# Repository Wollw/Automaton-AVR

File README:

Automaton AVR
====
This program simulates a Celullar Automaton with an AVR MCU connected to:
	(2) 4021 parallel->serial shift registers for reading
		survival rules from dip switches
	(2) 4021 parallel->serial shift registers for reading
		birth rules from dip switches
	(3) 4021 used to read initial cell state from
	(3) 74HC595 for controlling 24 different LEDs

Installation
----
Pick a configuration:
    $ cp cfg/myconfig.h src/config.h

To build:
    $ make

To upload:
    $ make program

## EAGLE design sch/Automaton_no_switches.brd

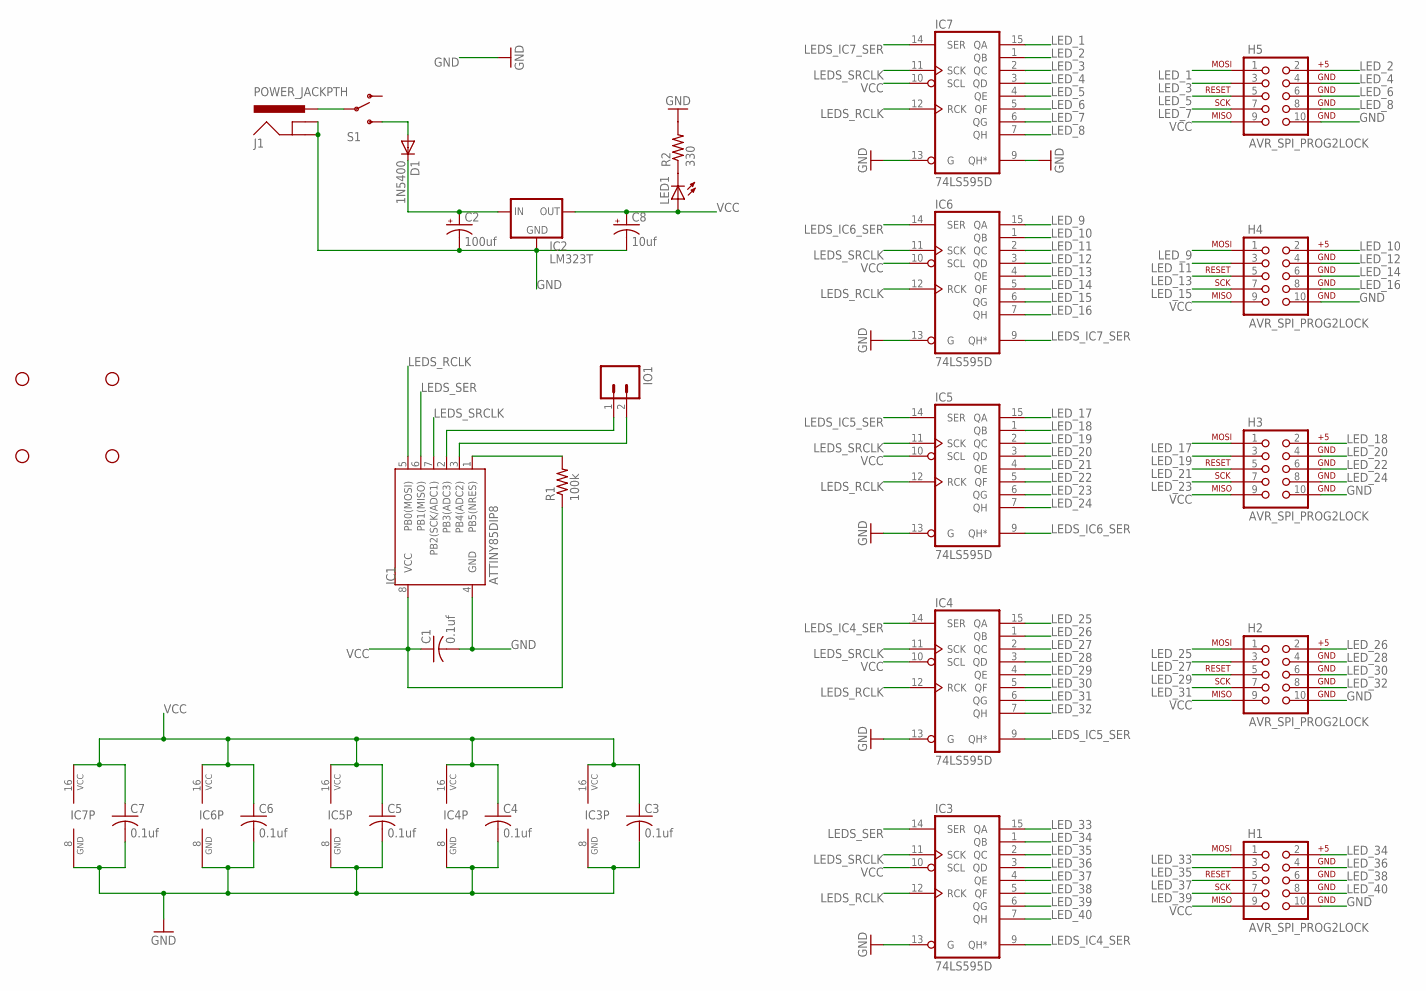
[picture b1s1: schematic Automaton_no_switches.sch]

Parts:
C1, C3, C4, C5, C6, C7: 0.1uf; C1206
C2: 100uf; E5-10,5
C8: 10uf; E2-5
D1: 1N5400; DO201-15
H1, H2, H3, H4, H5: AVR_SPI_PROG2LOCK; 2X5-SHROUDED_LOCK
HOLE1, HOLE2, HOLE3, HOLE4: STAND-OFF
IC1: ATTINY85DIP8; DIP08
IC2: LM323T; TO220-IGO
IC3, IC4, IC5, IC6, IC7: 74LS595D; SO16
IO1: M02PTH3; 1X02_LONGPADS
J1: POWER_JACKPTH; POWER_JACK_PTH
LED1: LEDSMT1206; 1206
R1: 100k; M1206
R2: 330; M1206
S1: SWITCH-SPDTPTH_LOCK; SWITCH-SPDT_LOCK.007S

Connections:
GND: C1.2, C2.-, C3.2, C4.2, C5.2, C6.2, C7.2, C8.-, H1.10, H2.10, H3.10, H4.10, H5.10, IC1.4 (GND), IC2.GND, IC3.8 (GND), IC3.13 (G), IC4.8 (GND), IC4.13 (G), IC5.8 (GND), IC5.13 (G), IC6.8 (GND), IC6.13 (G), IC7.8 (GND), IC7.9 (QH*), IC7.13 (G), J1.GND, J1.GNDBREAK, R2.2
LEDS_IC4_SER: IC3.9 (QH*), IC4.14 (SER)
LEDS_IC5_SER: IC4.9 (QH*), IC5.14 (SER)
LEDS_IC6_SER: IC5.9 (QH*), IC6.14 (SER)
LEDS_IC7_SER: IC6.9 (QH*), IC7.14 (SER)
LEDS_RCLK: IC1.5 (PB0(MOSI)), IC3.12 (RCK), IC4.12 (RCK), IC5.12 (RCK), IC6.12 (RCK), IC7.12 (RCK)
LEDS_SER: IC1.6 (PB1(MISO)), IC3.14 (SER)
LEDS_SRCLK: IC1.7 (PB2(SCK/ADC1)), IC3.11 (SCK), IC4.11 (SCK), IC5.11 (SCK), IC6.11 (SCK), IC7.11 (SCK)
LED_1: H5.1, IC7.15 (QA)
LED_2: H5.2, IC7.1 (QB)
LED_3: H5.3, IC7.2 (QC)
LED_4: H5.4, IC7.3 (QD)
LED_5: H5.5, IC7.4 (QE)
LED_6: H5.6, IC7.5 (QF)
LED_7: H5.7, IC7.6 (QG)
LED_8: H5.8, IC7.7 (QH)
LED_9: H4.1, IC6.15 (QA)
LED_10: H4.2, IC6.1 (QB)
LED_11: H4.3, IC6.2 (QC)
LED_12: H4.4, IC6.3 (QD)
LED_13: H4.5, IC6.4 (QE)
LED_14: H4.6, IC6.5 (QF)
LED_15: H4.7, IC6.6 (QG)
LED_16: H4.8, IC6.7 (QH)
LED_17: H3.1, IC5.15 (QA)
LED_18: H3.2, IC5.1 (QB)
LED_19: H3.3, IC5.2 (QC)
LED_20: H3.4, IC5.3 (QD)
LED_21: H3.5, IC5.4 (QE)
LED_22: H3.6, IC5.5 (QF)
LED_23: H3.7, IC5.6 (QG)
LED_24: H3.8, IC5.7 (QH)
LED_25: H2.1, IC4.15 (QA)
LED_26: H2.2, IC4.1 (QB)
LED_27: H2.3, IC4.2 (QC)
LED_28: H2.4, IC4.3 (QD)
LED_29: H2.5, IC4.4 (QE)
LED_30: H2.6, IC4.5 (QF)
LED_31: H2.7, IC4.6 (QG)
LED_32: H2.8, IC4.7 (QH)
LED_33: H1.1, IC3.15 (QA)
LED_34: H1.2, IC3.1 (QB)
LED_35: H1.3, IC3.2 (QC)
LED_36: H1.4, IC3.3 (QD)
LED_37: H1.5, IC3.4 (QE)
LED_38: H1.6, IC3.5 (QF)
LED_39: H1.7, IC3.6 (QG)
LED_40: H1.8, IC3.7 (QH)
unnamed: C2.+, D1.C, IC2.IN
unnamed: IC1.1 (PB5(NRES)), R1.2
unnamed: J1.PWR, S1.2
unnamed: D1.A, S1.3 (S)
unnamed: LED1.C, R2.1
PB3: IC1.2 (PB3(ADC3)), IO1.1
PB4: IC1.3 (PB4(ADC2)), IO1.2
VCC: C1.1, C3.1, C4.1, C5.1, C6.1, C7.1, C8.+, H1.9, H2.9, H3.9, H4.9, H5.9, IC1.8 (VCC), IC2.OUT, IC3.10 (SCL), IC3.16 (VCC), IC4.10 (SCL), IC4.16 (VCC), IC5.10 (SCL), IC5.16 (VCC), IC6.10 (SCL), IC6.16 (VCC), IC7.10 (SCL), IC7.16 (VCC), LED1.A, R1.1

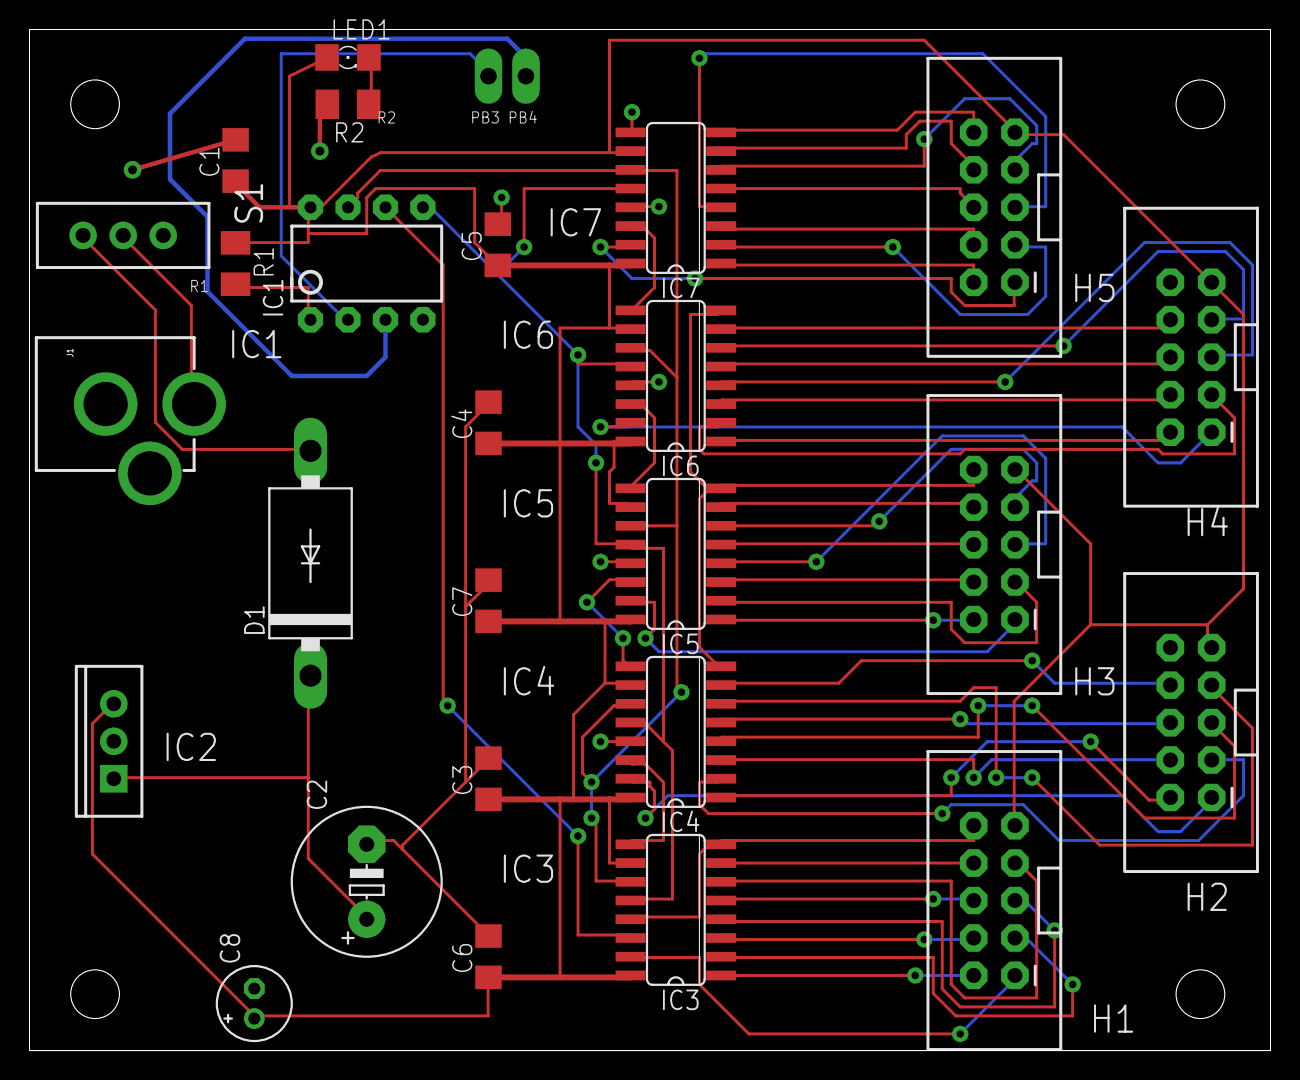
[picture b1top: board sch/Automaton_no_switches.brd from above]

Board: 2 copper layers, 84.1 x 69.2 mm, 31 parts (0 on the bottom side), 56 nets.

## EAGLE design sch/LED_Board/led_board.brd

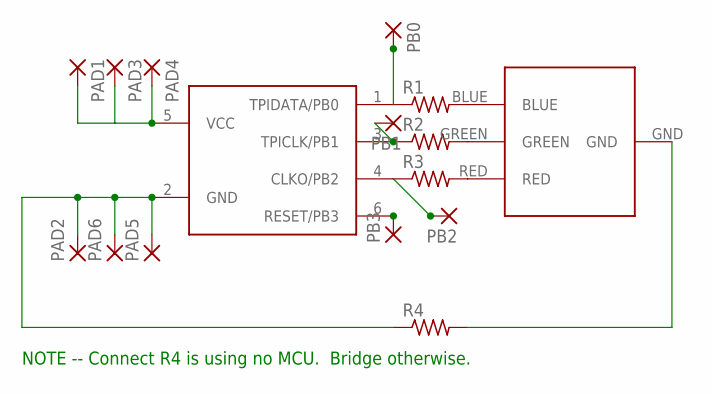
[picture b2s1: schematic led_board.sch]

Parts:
PAD1, PAD2, PAD3, PAD4, PAD5, PAD6: 1,6/0,8
PB0, PB1, PB2, PB3: 1,6/0,8
R1, R2, R3, R4: R-US_M1206; M1206
U$1: BIVAR-RGB-LED; 7.6X7.6MM-LED
U$2: ATTINY10SOT; SOT23-6

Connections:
unnamed: PAD2.1, PAD5.1, PAD6.1, R4.1, U$2.2 (GND)
unnamed: R1.2, U$1.BLUE
unnamed: R2.2, U$1.GREEN
unnamed: R3.2, U$1.RED
unnamed: R4.2, U$1.GND
PB0: PB0.1, R1.1, U$2.1 (TPIDATA/PB0)
PB1: PB1.1, R2.1, U$2.3 (TPICLK/PB1)
PB2: PB2.1, R3.1, U$2.4 (CLKO/PB2)
PB3: PB3.1, U$2.6 (RESET/PB3)
VCC: PAD1.1, PAD3.1, PAD4.1, U$2.5 (VCC)

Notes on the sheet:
NOTE -- Connect R4 is using no MCU. Bridge otherwise.

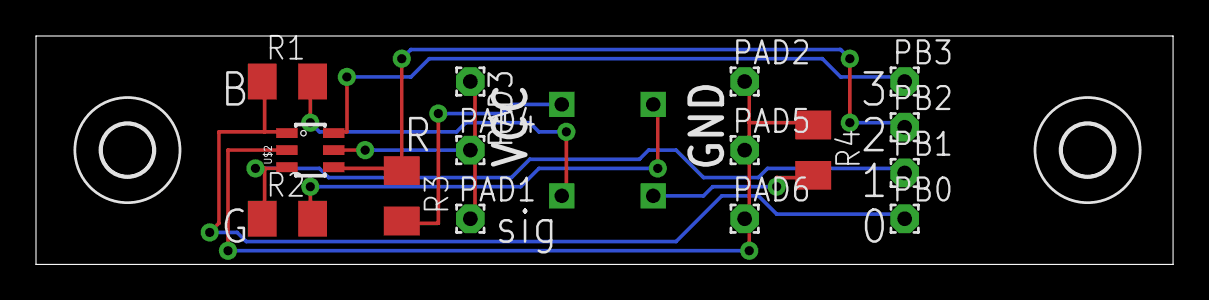
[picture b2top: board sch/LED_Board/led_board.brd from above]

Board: 2 copper layers, 63.2 x 12.7 mm, 18 parts (1 on the bottom side), 10 nets.

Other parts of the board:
E$1, E$2: 2,8

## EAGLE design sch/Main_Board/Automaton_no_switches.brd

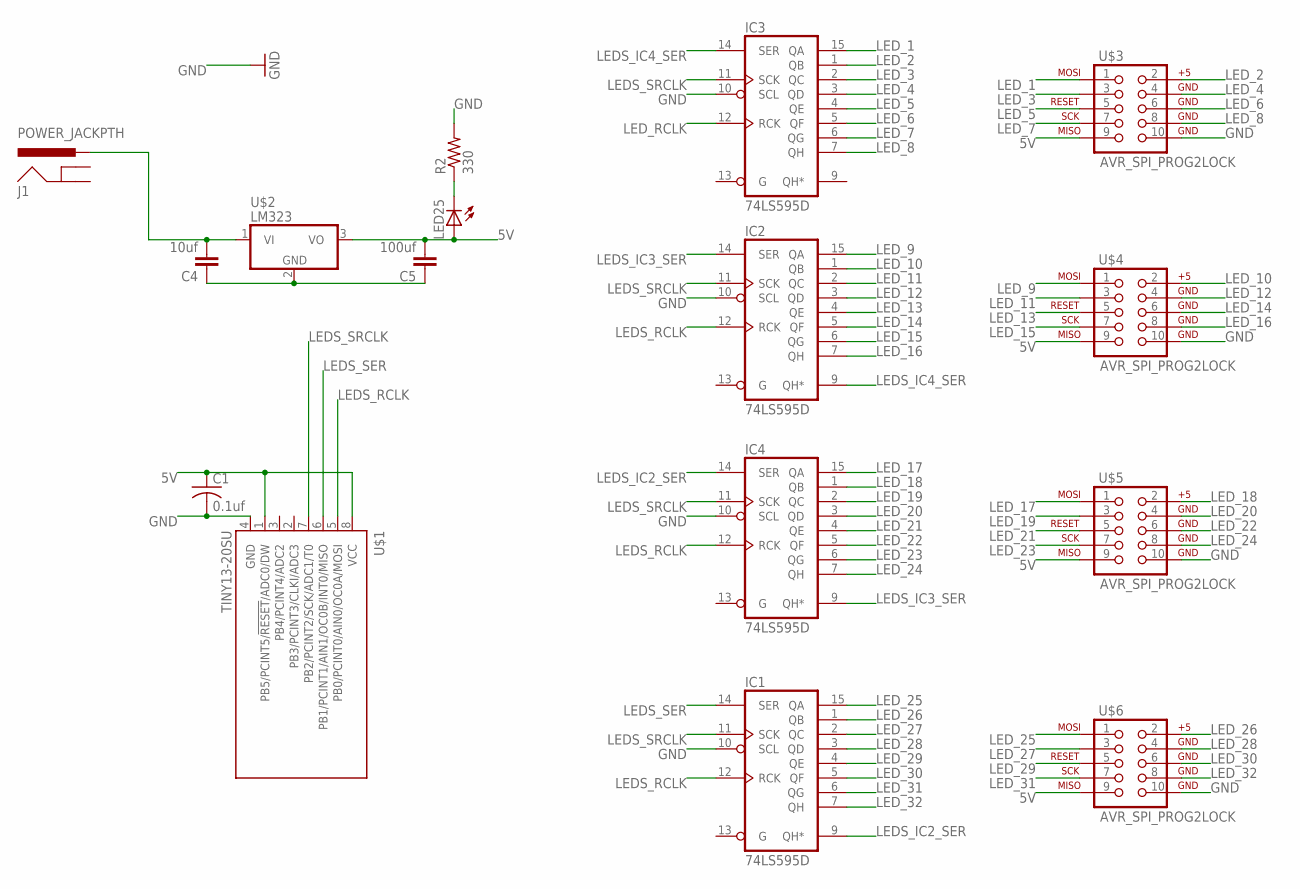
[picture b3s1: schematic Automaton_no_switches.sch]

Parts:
C1: 0.1uf; C025-024X044
C4: 10uf; 1210
C5: 100uf; 1210
IC1, IC2, IC3, IC4: 74LS595D; SO16
J1: POWER_JACKPTH; POWER_JACK_PTH
LED25: LED; SMARTLED-TTW
R2: 330; 0204/5
U$1: TINY13-20SU; 8S2
U$2: LM323; TO220H
U$3, U$4, U$5, U$6: AVR_SPI_PROG2LOCK; 2X5-SHROUDED_LOCK

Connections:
5V: C1.1, C5.2, LED25.A@1 (A), U$1.1 (PB5/PCINT5/!RESET!/ADC0/DW), U$1.8 (VCC), U$2.3 (VO), U$3.9, U$4.9, U$5.9, U$6.9
GND: C1.2, IC1.8 (GND), IC1.10 (SCL), IC2.8 (GND), IC2.10 (SCL), IC3.8 (GND), IC3.10 (SCL), IC4.8 (GND), IC4.10 (SCL), R2.2, U$1.4 (GND), U$3.10, U$4.10, U$5.10, U$6.10
LEDS_IC2_SER: IC1.9 (QH*), IC4.14 (SER)
LEDS_IC3_SER: IC2.14 (SER), IC4.9 (QH*)
LEDS_IC4_SER: IC2.9 (QH*), IC3.14 (SER)
LEDS_RCLK: IC1.12 (RCK), IC2.12 (RCK), IC4.12 (RCK), U$1.5 (PB0/PCINT0/AIN0/OC0A/MOSI)
LEDS_SER: IC1.14 (SER), U$1.6 (PB1/PCINT1/AIN1/OC0B/INT0/MISO)
LEDS_SRCLK: IC1.11 (SCK), IC2.11 (SCK), IC3.11 (SCK), IC4.11 (SCK), U$1.7 (PB2/PCINT2/SCK/ADC1/T0)
LED_1: IC3.15 (QA), U$3.1
LED_2: IC3.1 (QB), U$3.2
LED_3: IC3.2 (QC), U$3.3
LED_4: IC3.3 (QD), U$3.4
LED_5: IC3.4 (QE), U$3.5
LED_6: IC3.5 (QF), U$3.6
LED_7: IC3.6 (QG), U$3.7
LED_8: IC3.7 (QH), U$3.8
LED_9: IC2.15 (QA), U$4.1
LED_10: IC2.1 (QB), U$4.2
LED_11: IC2.2 (QC), U$4.3
LED_12: IC2.3 (QD), U$4.4
LED_13: IC2.4 (QE), U$4.5
LED_14: IC2.5 (QF), U$4.6
LED_15: IC2.6 (QG), U$4.7
LED_16: IC2.7 (QH), U$4.8
LED_17: IC4.15 (QA), U$5.1
LED_18: IC4.1 (QB), U$5.2
LED_19: IC4.2 (QC), U$5.3
LED_20: IC4.3 (QD), U$5.4
LED_21: IC4.4 (QE), U$5.5
LED_22: IC4.5 (QF), U$5.6
LED_23: IC4.6 (QG), U$5.7
LED_24: IC4.7 (QH), U$5.8
LED_25: IC1.15 (QA), U$6.1
LED_26: IC1.1 (QB), U$6.2
LED_27: IC1.2 (QC), U$6.3
LED_28: IC1.3 (QD), U$6.4
LED_29: IC1.4 (QE), U$6.5
LED_30: IC1.5 (QF), U$6.6
LED_31: IC1.6 (QG), U$6.7
LED_32: IC1.7 (QH), U$6.8
LED_RCLK: IC3.12 (RCK)
unnamed: C4.2, J1.PWR, U$2.1 (VI)
unnamed: C4.1, C5.1, U$2.2 (GND)
unnamed: LED25.C@1 (C), R2.1
VCC: IC1.16 (VCC), IC2.16 (VCC), IC3.16 (VCC), IC4.16 (VCC)

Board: 2 copper layers, 16 parts (0 on the bottom side), 44 nets, no tracks yet.

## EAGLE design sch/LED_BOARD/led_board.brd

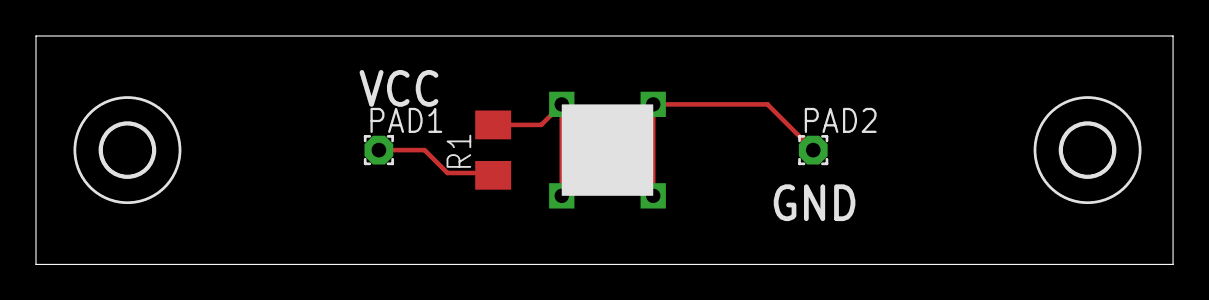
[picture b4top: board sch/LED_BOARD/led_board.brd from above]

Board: 2 copper layers, 63.2 x 12.7 mm, 6 parts (0 on the bottom side), 3 nets.

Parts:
E$1, E$2: 2,8
PAD1, PAD2: 1,6/0,8
R1: M1206
U$1: 7.6X7.6_LED; 7.6X7.6MM_LED

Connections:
GND: PAD2.1, U$1.GND1, U$1.GND2
unnamed: R1.2, U$1.VCC1, U$1.VCC2
VCC: PAD1.1, R1.1

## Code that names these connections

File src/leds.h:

#pragma once
#include <stdlib.h>
#include <stdint.h>
#include "petridish.h"

// shift registers (74HC595) for LEDs
#define LEDS_SHIFT_REG_COUNT	3

// Serial->Parallel for LEDs - Might change to PORTC to leave SPI open
#define LEDS_DDR	DDRB
#define LEDS_PORT   PORTB
#define LEDS_RCLK   PB0
#define LEDS_SER	PB1
#define LEDS_SRCLK  PB2

// Functions for interacting with the output for leds
// See leds.c for details
void leds_shift_init(void);
void leds_change_state(uint64_t new_state, uint8_t pins_to_shift);

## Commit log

2011-08-23 comment changes
2011-08-23 accidently committed the wrong thing before
2011-08-24 Cleaned the code up a bit and uses less memory.
2011-08-24 fixed gitignore file
2011-08-24 Changed ms_delay to scale based on defined MHZ. It only worked properly at 1MHz before.
2011-08-24 added using clock interrupt to TODO list
2011-08-24 multiple versions now
2011-08-28 Forgot a call to free
2011-08-28 fixing last commit, added to TODO list
2011-08-28 removing penrose as submodule. It was never meant to be one to begin with...
2011-08-29 oops... I called it penrose but it's actually the polygon automaton...
2011-08-30 Lots of fixes... still not quite working but thought I'd commit anyway. Using bitmaps instead of full variables for setting neighbors to save memory, divided much of the program into different functi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
2011-08-31 Everything works. Yay\!
2011-08-31 Changes rules to use an if statement with a rotated and AND'ed bitmask instead of a switch statement.
2011-08-31 moved initial state to a bitmask too
2011-08-31 mcu now assumed to be running at 1MHz
2011-08-31 added #define for staggering speed
2011-09-01 made STAGGER_DELAY_MS #define for defining the step of the stagger delay
2011-09-01 fixed a few small things and changed the way avr-size reports size data during make
2011-09-18 shift registers working in seperate program. still needs to be merged into main program (and I need to actually write the correct code for the piece I'm actually building too...)
2011-09-19 modularized the shift-registers program, created new directory for working on squares-and-triangles tessellation
2011-09-21 cleaned architecture a bit. added code for reading initial_state. new init code for the automaton. petridish_t data type acts as object for the automaton's state
2011-09-21 nothing major. commented out some redundant code
2011-09-23 WIP currently has a working Conway's blinker if rules dip switches are set to 2/23 rule set (Conway's Game of Life). Code for Initial State is present but untested and not currently in use as I haven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
2011-09-23 cleaned up debug code a bit. serial outputs the new petridish state after it calculates it
2011-09-23 cleaned source up a bit.
2011-09-23 deleted old parts of the project. cleaned up the build process a tad.
2011-09-23 added schematic that I'm working on. still largely incomplete
2011-10-03 cleaned main function a bit
2011-10-04 worked on schematic some more
2011-10-05 Done with schematic.
2011-10-05 Cleaned up schematic folder.
2011-10-16 Version 1! All the basics are in! DIP switches control rules and initial state. schematic is out of date.
2011-10-17 fixed some text in the readme
2011-10-17 Added BSD license.
2011-10-17 changed all expanded tabs to real tabs
2011-10-18 Using function pointers for petridish now. Makes for a larger program but I think it's cleaner. Also added a lot more comments.
2011-10-18 changed suffix of readme
2011-10-18 added README back
2011-10-18 renamed petridish struct to automaton. worked on comments more. working on making the automaton type more object like
2011-10-19 added configuration example and some text in readme. changed the way the automaton is created to malloc for a struct pointer; I think this is cleaner.
2011-10-19 added a comment in setup() in main.c
2011-10-19 added a task to TODO
2011-10-19 updated schematic
2011-11-04 made schematic and board layout for an LED breakout board.
2011-11-11 UNTESTED! --- Refactored code a bit. Took some methods out of petridish object (renamed automaton object to petridish). Moved LED code and Serial code out of petridish methods.
2011-11-16 created config.h file for the sculpture I'm currently building for class
2011-11-18 Fixed an infinite loop in serial out function. config.h files can now define CONFIG_USE_SERIAL and CONFIG_USE_SWITCHES_FOR_SETTINGS to turn on serial output of petridish state and to read rules and i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
2011-11-19 more configuration options for using serial and switches and stuff
2011-11-20 Added a makefile for attiny85. fixed a missing malloc
2011-11-20 forgot to free the rules, fixed
2011-11-20 I think things work now...
2011-11-20 Removed extra cells from 3x3 config
2011-11-26 created gEDA schematic for 4-register board w/o switches
2011-11-26 updatd schematic
2011-12-02 finalized config for "Automaton 0x00" sculpture
2011-12-02 Added ADC read functionality, variable delays, and used these to implement an option for using an analog source such as a potentiometer to control the time between cell updates.
2011-12-07 better documentation in README.md
2011-12-08 cleaned up config files a bit
2011-12-08 Added serial baudrate configuration setting to the config.h files
2011-12-08 fixed analog input for ATmega328P by making it reference AVCC
2011-12-08 removed extra serial write
2012-01-20 More work on schematics. Using EAGLE exclusively for now... Changed LED board to allow for an attiny4/5/9/10 with a signal pin and to use an RGB led.
2012-01-20 More schematic work. Make a potentially working board for the main automaton circuit.
2012-01-22 Added breakout for PB pins on attiny10 on the LED controller.
2012-01-31 Changed to using uint64_t instead of uint32_t so I can use more than 32 cells... Also aliased "make program" to "make install" because I keep typing "make install" on accident.
2012-01-31 Updated README.md to reflect the change from uint32_t to uint64_t. I also forgot to mention the change of the rules variables from uint16_t to uint32_t before and this was changed in the readme too.
2012-02-17 fixed typo in schematic, removed extra text from board
2012-02-19 changed license to unlicense
2012-02-19 changed license
2012-02-19 fixed years in license
2012-02-19 moved LED board schematics to the LED PWM Controller repo
2012-02-25 added parts list
2012-02-25 added note about current to PARTS list
2012-02-25 added to schematic
2012-02-26 board passes batchpcb's DRC now
2012-02-26 reduced the board size, added some parts to the schematic and board (power switch, breakout for unused MCU pins, power LED)
2012-04-02 removed all code form repository and redirecting to new project.
2012-05-29 added gh-pages redirect
2012-05-29 fixed url

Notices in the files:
parts and their libraries:
SparkFun-PowerIC: Licensing: CC v3.0 Share-Alike You are welcome to use this library for commercial purposes.
